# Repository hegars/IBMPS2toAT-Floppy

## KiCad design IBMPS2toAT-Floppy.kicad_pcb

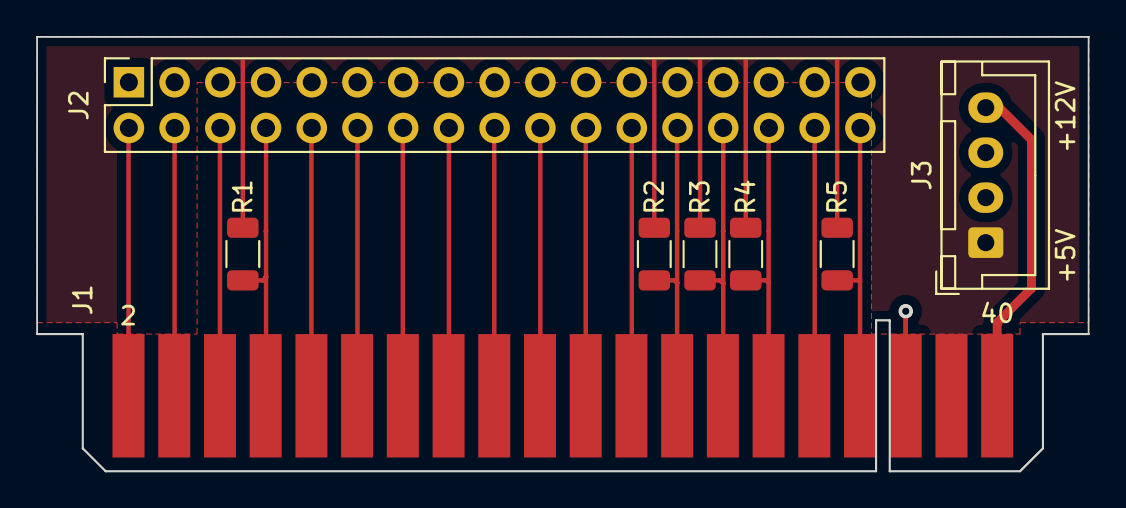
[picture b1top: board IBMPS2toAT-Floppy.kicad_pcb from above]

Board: 2 copper layers, 58.4 x 24.1 mm, 8 parts (0 on the bottom side), 21 nets.

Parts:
J1: Conn_02x20_Odd_Even; IBM_2x20_EDGE
J2: Conn_02x14_Odd_Even; PinSocket_2x17_P2.54mm_Vertical
J3: Conn_01x04; JST_XH_B4B-XH-A_1x04_P2.50mm_Vertical
R1, R2, R3, R4, R5: R_Small; R_1206_3216Metric

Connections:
+5V: J1.38, J3.1, R1.2, R2.2, R3.2, R4.2, R5.2
+12V: J1.40, J3.4
GND: J1.1, J1.5, J1.7, J1.9, J1.11, J1.13, J1.15, J1.17, J1.19, J1.21, J1.23, J1.25, J1.27, J1.29, J1.31, J1.33, J1.37, J1.39, J2.1, J2.5, J2.7, J2.9, J2.11, J2.13, J2.15, J2.17, J2.19, J2.21, J2.23, J2.25, J2.27, J2.29, J2.31, J2.33, J3.2, J3.3
RESERVED-1: J1.4, J2.4
RESERVED-2: J1.6, J2.6
XLINK: J1.35, J1.36
~DIR: J1.18, J2.18
~DRVSB-0: J1.14, J2.14
~DRVSB-1: J1.12, J2.12
~DSKGHG: J1.34, J2.34, R5.1
~INDEX: J1.8, J2.8, R1.1
~MOTEA: J1.10, J2.10
~MOTEB: J1.16, J2.16
~RDATA: J1.30, J2.30, R4.1
~REDWC: J1.2, J2.2
~SIDE1: J1.32, J2.32
~STEP: J1.20, J2.20
~TRK00: J1.26, J2.26, R2.1
~WDATA: J1.22, J2.22
~WGATE: J1.24, J2.24
~WPT: J1.28, J2.28, R3.1

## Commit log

2022-10-09 rev1
2022-10-09 image update
